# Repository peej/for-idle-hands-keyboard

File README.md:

For Idle Hands is a 6x4x2 key ortholinear split keyboard PCB.

The goal of this project is to build a Let's Split keyboard clone from sub-100x100mm PCB boards.:

* Designed to be easy to build with minimal soldering experience.
* Switch plate cutouts in the PCB so the same PCB can also be used as a switch plate.
* Serial communication over a TRRS cable.
* Single sided PCB, so both halves of the keyboard are identical.

# Bill of Materials (BOM)

* 8 PCBs, 4 for components and 4 as switch plates.
* 48 MX compatible switches.
* 48 1n4148 diodes.
* 2 Pro Micro controllers with headers or DIP sockets.
* 2 PJ320A 3.5mm TRRS jacks.
* TRRS cable and micro USB cable.
* 8 2M standoffs (12mm, depending on required height)
* 16 2M screws
* 48 MX compatible key caps.

## Tools

* Hacksaw blade or similar
* Flat edged file or sanding paper
* Soldering iron and solder

# Ordering PCBs

PCBs can be manufactuered by a variety of online PCB fabricators. You can use [PCBShopper](https://pcbshopper.com/) to search for the best price.

The zip file in the gerber directory contains the gerber files your fabricator will need to make the PCB [for-idle-hands.zip](https://github.com/peej/for-split-keyboard/blob/master/gerber/for-idle-hands.zip) PCB.

When uploading the gerber zip files, use the default PCB settings. The plate PCB thickness should be 1.6mm for the switches to snap into the plate securely.

# Construction

* You will need 8 PCBs.
* If you are using the 6x4x2 layout, carefully cut the bottom row of switch footprints from the 4 PCBs.
* Use the hacksaw blade to remove the 4 support screw holes from the 2 component PCBs.
* Use a hacksaw blade to remove the cutouts for the switch plate PCBs.
* Solder the diodes onto the underside of each PCB.
* Solder on the Pro Micro headers (or a 24 pin DIP socket) onto the underside of each PCB, do not solder on the Pro Micros yet.
* Solder the PJ320A TRRS sockets onto the underside of each PCB.
  * There are 2 positions per board, use the right position on the left hand PCB and the left position on the right hand PCB.
  * Ensure that the pins will not foul the placement of the switches and still allow the switches to sit flat on the PCB.
  * You may need to slightly bend the pins inwards away from the switch footprint.
* Insert the switches into the plate and then into the top of the PCBs.
  * Insert all the switches and ensure that the pins of each switch are correctly coming through the board and are not bent under the PCB.
  * The top switch that sits underneath the Pro Micro can be inserted in either a north or south facing orientation. North facing helps to prevent it shorting on the Pro Micro components.
* Solder all the switch pins.
* Solder on the Pro Micros, ensure that you get them the correct way around, the chip side should be face down towards the PCB.
* Attach the standoffs to the plate PCB with the screws.
* Connect the halves together with the TRRS cable.
* Flash both Pro Micros with the firmware, see the [QMK documentation](http://qmk.fm/) on how to build and flash the firmware.

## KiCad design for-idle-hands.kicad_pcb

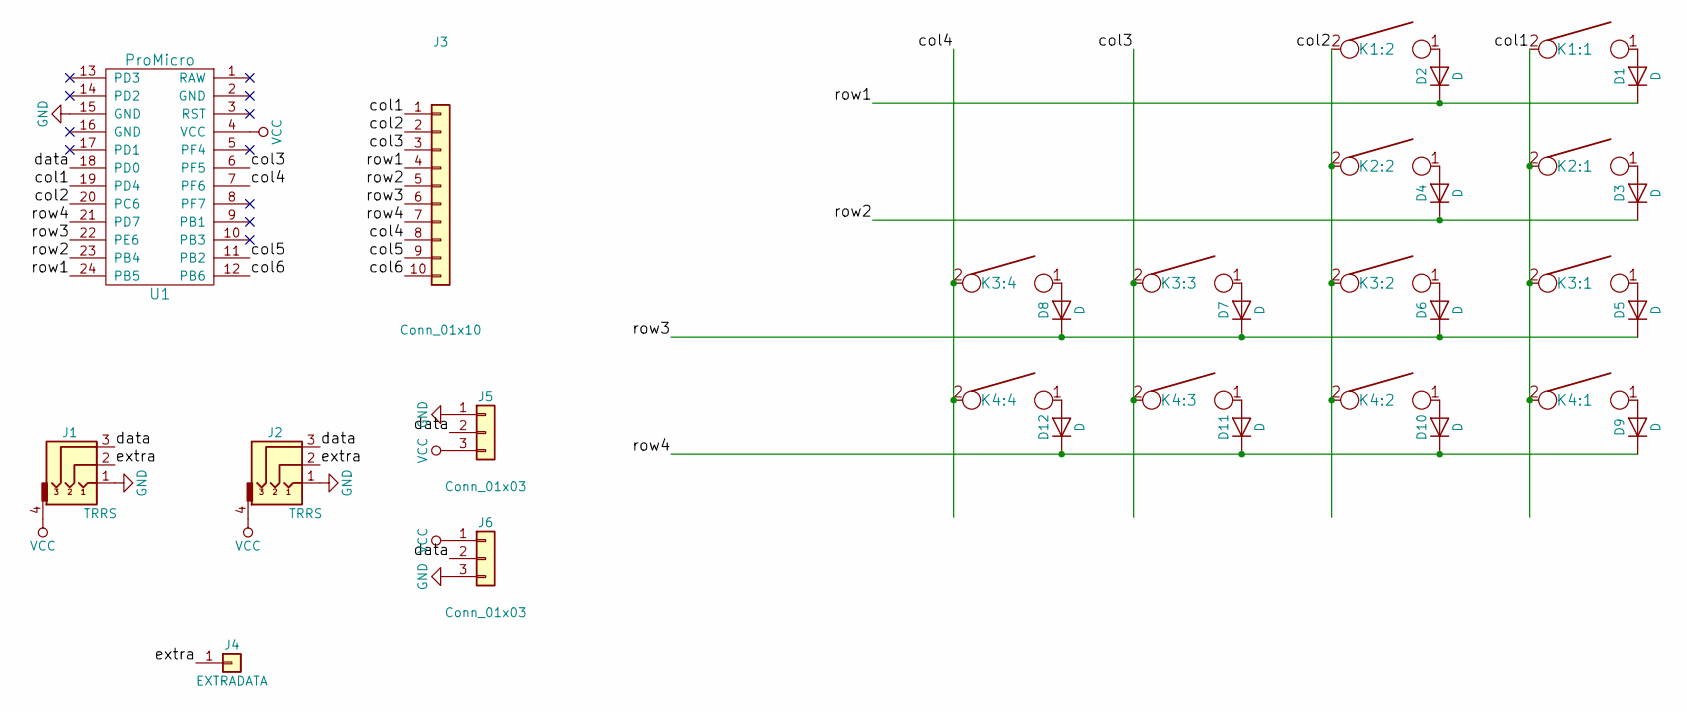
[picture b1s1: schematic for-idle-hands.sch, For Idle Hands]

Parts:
D1, D2, D3, D4, D5, D6, D7, D8, D9, D10, D11, D12: D; DIODE
J1, J2: TRRS; PJ-320A
J3: Conn_01x10; CONNECTOR_10
J4: EXTRADATA; Pin_Header_Straight_1x01_Pitch1.00mm
J5, J6: Conn_01x03; CONNECTOR_3
K1:1: K5; MX_CUTOUT
K1:2: K4; MX_CUTOUT
K2:1: K15; MX_CUTOUT
K2:2: K14; MX_CUTOUT
K3:1: K25; MX_CUTOUT
K3:2: K24; MX_CUTOUT
K3:3: K23; MX_CUTOUT
K3:4: K22; MX_CUTOUT
K4:1: K35; MX_CUTOUT
K4:2: K34; MX_CUTOUT
K4:3: K33; MX_CUTOUT
K4:4: K32; MX_CUTOUT
U1: ProMicro; Pro_Micro_ChipSideDown

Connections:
/col1: J3.1, K1:1.2, K2:1.2, K3:1.2, K4:1.2, U1.19 (PD4)
/col2: J3.2, K1:2.2, K2:2.2, K3:2.2, K4:2.2, U1.20 (PC6)
/col3: J3.3, K3:3.2, K4:3.2, U1.6 (PF5)
/col4: J3.8, K3:4.2, K4:4.2, U1.7 (PF6)
/col5: J3.9, U1.11 (PB2)
/col6: J3.10, U1.12 (PB6)
/data: J1.3, J2.3, J5.2, J6.2, U1.18 (PD0)
/extra: J1.2, J2.2, J4.1
/row1: D1.1 (K), D2.1 (K), J3.4, U1.24 (PB5)
/row2: D3.1 (K), D4.1 (K), J3.5, U1.23 (PB4)
/row3: D5.1 (K), D6.1 (K), D7.1 (K), D8.1 (K), J3.6, U1.22 (PE6)
/row4: D9.1 (K), D10.1 (K), D11.1 (K), D12.1 (K), J3.7, U1.21 (PD7)
GND: J1.1, J2.1, J5.1, J6.3, U1.15 (GND)
unnamed: D1.2 (A), K1:1.1
unnamed: D2.2 (A), K1:2.1
unnamed: D3.2 (A), K2:1.1
unnamed: D4.2 (A), K2:2.1
unnamed: D5.2 (A), K3:1.1
unnamed: D6.2 (A), K3:2.1
unnamed: D7.2 (A), K3:3.1
unnamed: D8.2 (A), K3:4.1
unnamed: D9.2 (A), K4:1.1
unnamed: D10.2 (A), K4:2.1
unnamed: D11.2 (A), K4:3.1
unnamed: D12.2 (A), K4:4.1
VCC: J1.4, J2.4, J5.3, J6.1, U1.4 (VCC)

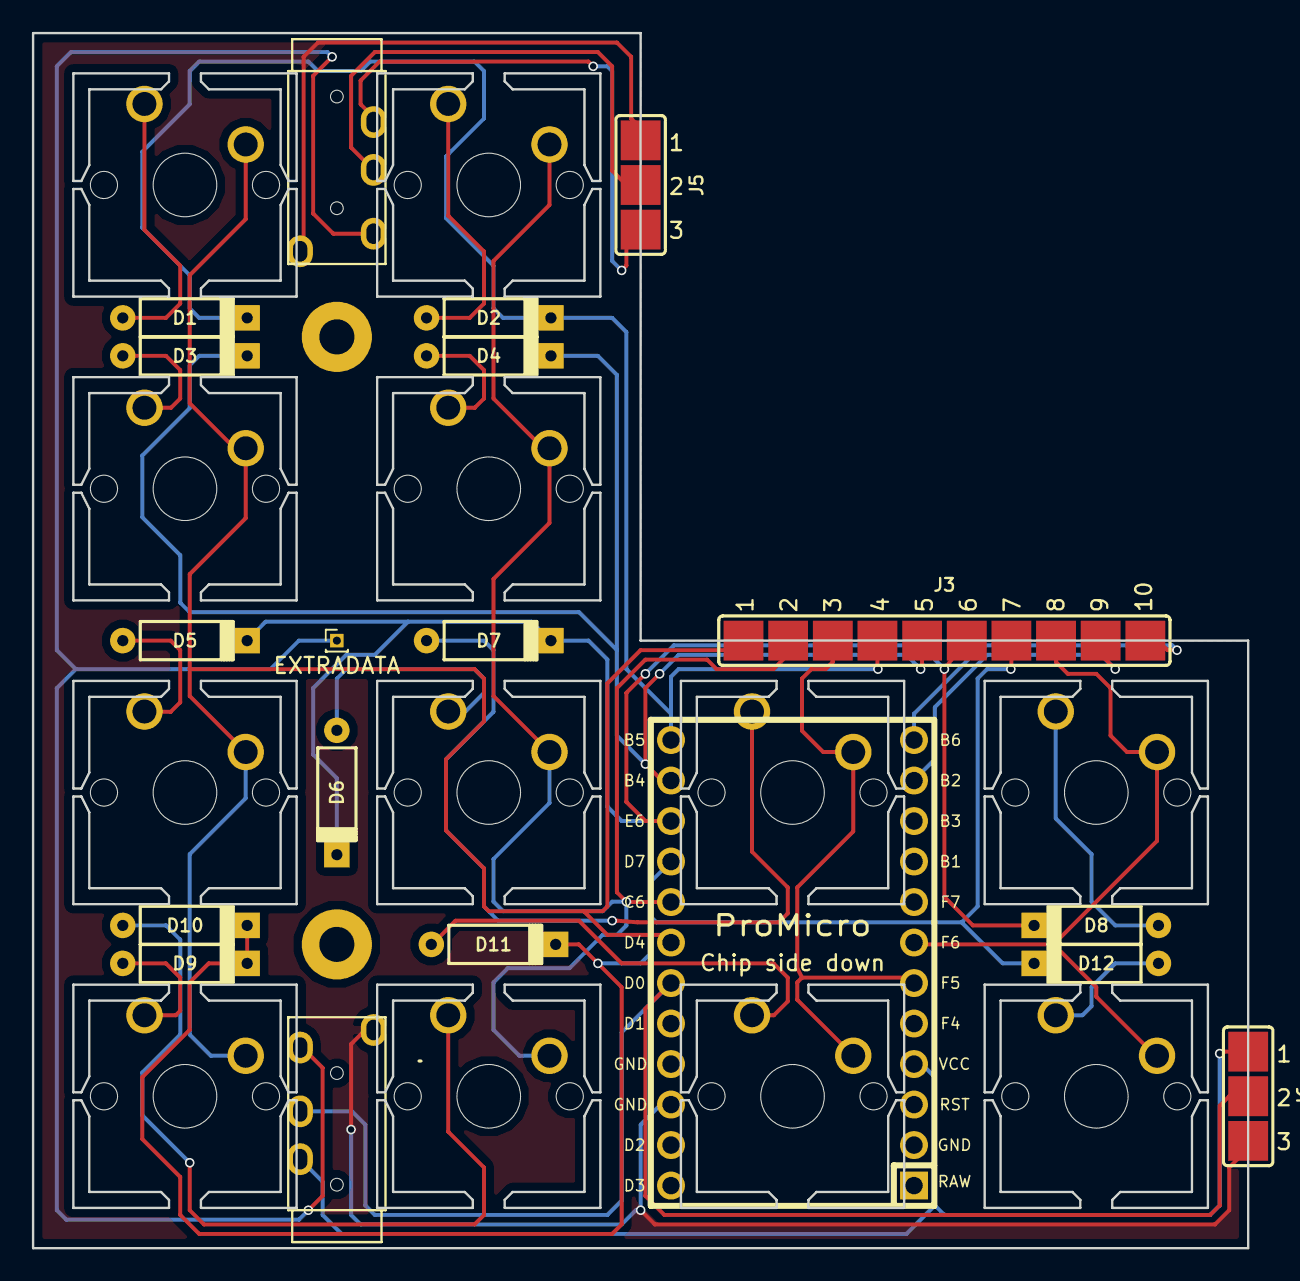
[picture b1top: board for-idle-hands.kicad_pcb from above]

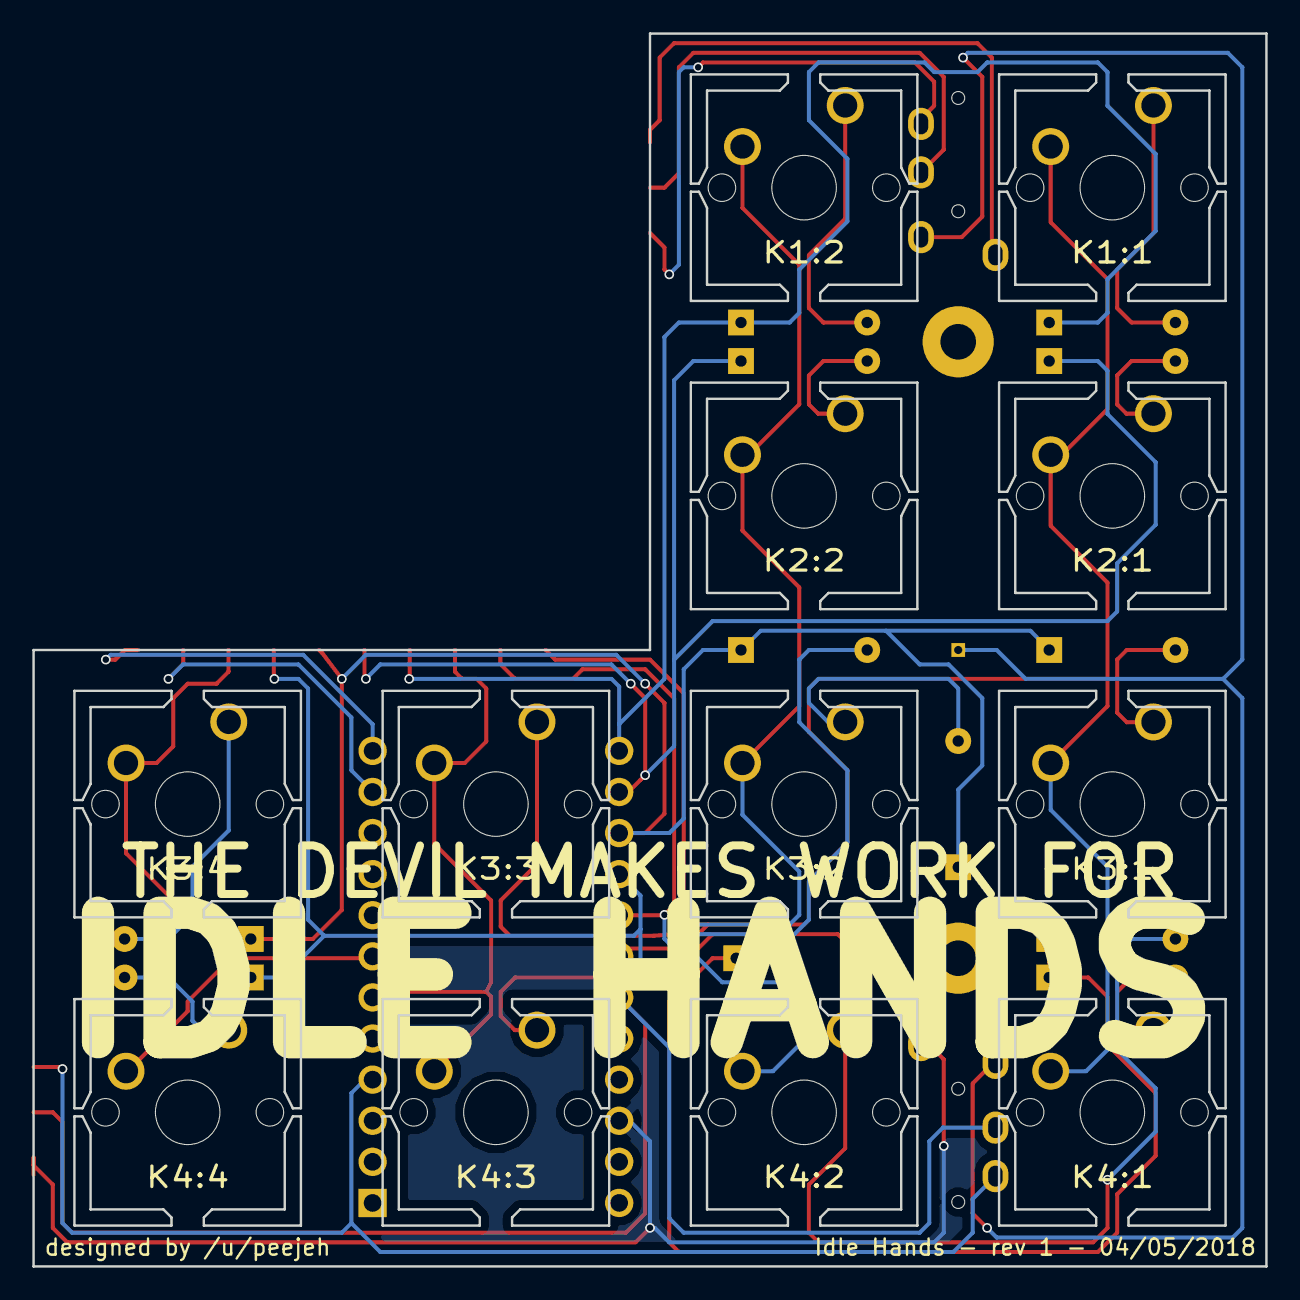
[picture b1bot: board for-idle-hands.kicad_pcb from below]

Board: 2 copper layers, 76.2 x 76.2 mm, 31 parts (12 on the bottom side), 26 nets.

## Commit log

2018-06-04 Add footprints
2018-06-04 Add schematic and PCB design
